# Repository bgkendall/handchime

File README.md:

# HandSTaMp

## Bill of Materials

| Reference | Silkscreen | Part                        | Footprint | Purpose                                        |
|-----------|------------|-----------------------------|-----------|------------------------------------------------|
| C1, C2    | 1µF        | 2 × 1µF ceramic capacitors  | 0603      | Decoupling capacitors for U3                   |
| C3        | 4µ7F       | 4.7µF ceramic capacitor     | 0603      | Bulk decoupling capacitor for U1               |
| C4        | 100nF      | 100nF ceramic capacitor     | 0603      | Decoupling capacitor for U1                    |
| C5        | 100nF      | 100nF ceramic capacitor     | 0603      | Unwanted reset prevention                      |
| D1        | D1         | PMEG2010EA Schottky diode   | SOD-323   | Reverse current protection                     |
| D2, D3    | D2, D3     | 2 × 1N4148 diodes           | SOD-123   | Matrix diodes for SW1/SW2                      |
| F1        | F1         | 500mA fuse                  | 0603      | Current overload protection                    |
| J1        | J1         | HRO TYPE-C-31-M-12 USB port |           | For the pluggings in of USB cables             |
| R1, R2    | 1, 2       | 2 × 5.1kΩ resistors         | 0603      | USB power negotiation (Rd) resistors           |
| R3        | 5k1Ω – P   | 5.1kΩ resistor              | 0603      | OPTIONAL 5V pull-up for RGB data line¹         |
| R4        | 1万Ω       | 10kΩ resistor               | 0603      | Prevention of unwanted boot state              |
| S1, S2    | *None*     | 2 × MX-compatible switches  | MX plate² | Keys for row 0, columns 0/1; mountings for PCB |
| U1        | U1         | STM32C071GBU6               | UFQFPN-28 | ~~Braaaains!~~ Microcontroller                 |
| U2        | U2         | PRTR5V0U2X                  | SOT-143   | ESD protection                                 |
| U3        | U3         | XC6206P332MR-G LDO          | SOT-23-3  | 5V to 3.3V step-down for U1                    |

##### Notes

 1. Remove/do not place R3 (“P”) if not using pin PB0 to drive RGB LEDs (e.g., as a regular matrix pin).
    Pin PB0 must be set to [open drain mode][open-drain].
 2. Three-pin “plate-mount” switches can be used as-is. To use five-pin “PCB-mount” switches,
    the two extra plastic alignment “pins” must be removed.

[open-drain]: https://docs.qmk.fm/drivers/ws2812#open-drain-circuit

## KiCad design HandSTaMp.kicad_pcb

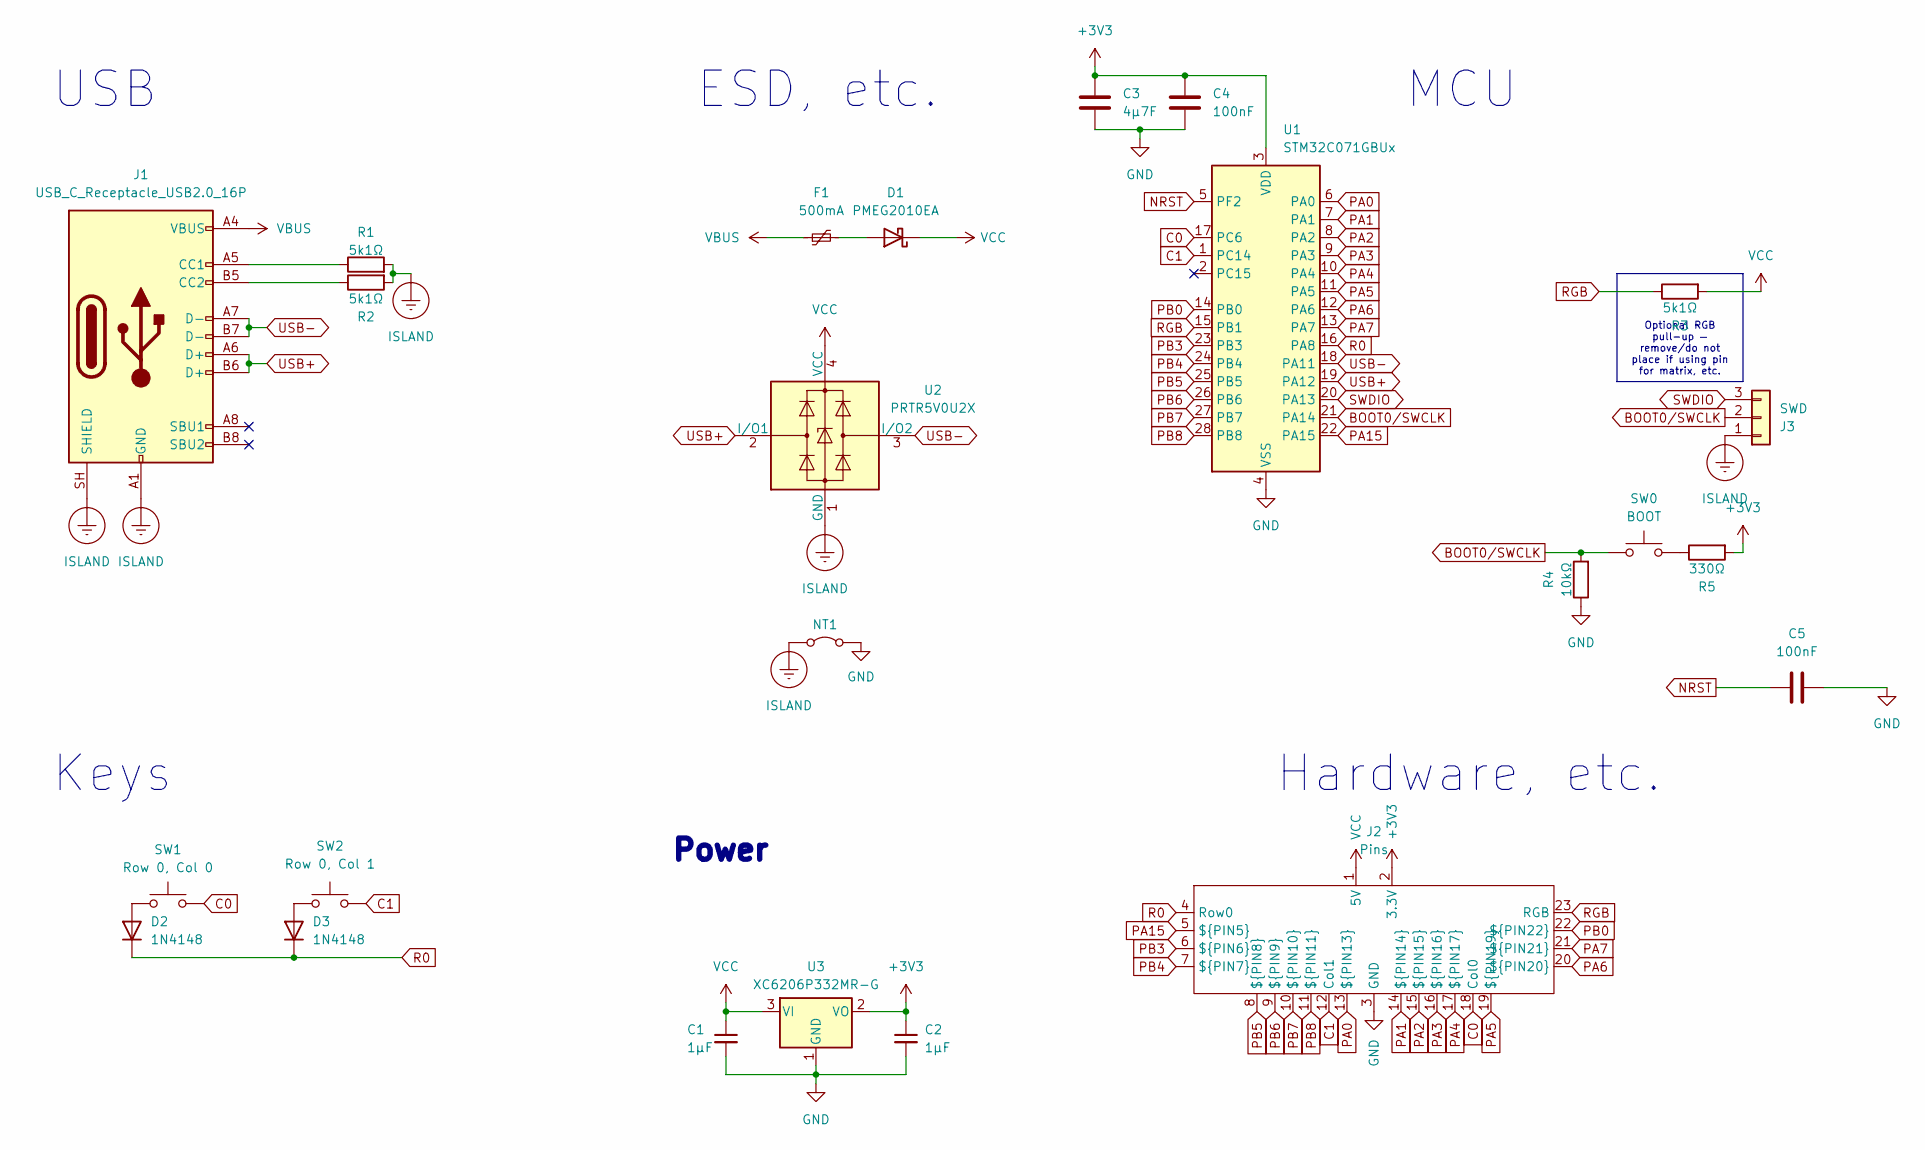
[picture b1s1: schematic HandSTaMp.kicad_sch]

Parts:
C1, C2: 1µF; C_0603_1608Metric; LCSC C52923
C3: 4µ7F; C_0603_1608Metric
C4, C5: 100nF; C_0603_1608Metric
D1: PMEG2010EA; D_SOD-323; LCSC C2837790
D2, D3: 1N4148; D_SOD-123
F1: 500mA; Fuse_0603_1608Metric; LCSC C210357
J1: USB_C_Receptacle_USB2.0_16P; USB_C_Receptacle_HRO_TYPE-C-31-M-12
J2: Pins; HandSTaMp
J3: SWD; SWD+GroundingPoint
NT1: Mounting Hole/Isolated Ground Jumper; NetTie-2_SMD_Pad0.5mm
R1, R2, R3: 5k1Ω; R_0603_1608Metric; LCSC C23186
R4: 10kΩ; R_0603_1608Metric; LCSC C23186
R5: 330Ω; R_0603_1608Metric; LCSC C23186
SW0: BOOT; SW_SPST_B3U-1000P; LCSC C231329
SW1: Row 0, Col 0; SW_MX_1u_PlateMount
SW2: Row 0, Col 1; SW_MX_1u_PlateMount
U1: STM32C071GBUx; QFN-28_4x4mm_P0.5mm
U2: PRTR5V0U2X; SOT-143; LCSC C12333
U3: XC6206P332MR-G; SOT-23-3

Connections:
+3V3: C2.1, C3.1, C4.1, J2.2 (3.3V), R5.2, U1.3 (VDD), U3.2 (VO)
BOOT0/SWCLK: J3.2, R4.2, SW0.1, U1.21 (PA14)
C0: J2.18 (Col0), SW1.1, U1.17 (PC6)
C1: J2.12 (Col1), SW2.1, U1.1 (PC14)
GND: C1.2, C2.2, C3.2, C4.2, C5.2, J2.3 (GND), NT1.2 (B), R4.1, U1.4 (VSS), U3.1 (GND)
ISLAND: J1.A1 (GND), J1.A12 (GND), J1.B1 (GND), J1.B12 (GND), J1.SH (SHIELD), J3.1, NT1.1 (A), R1.2, R2.2, U2.1 (GND)
NRST: C5.1, U1.5 (PF2)
unnamed: D1.2 (A), F1.2
unnamed: D2.2 (A), SW1.2
unnamed: D3.2 (A), SW2.2
unnamed: J1.A5 (CC1), R1.1
unnamed: J1.B5 (CC2), R2.1
unnamed: R5.1, SW0.2
PA0: J2.13 (${PIN13}), U1.6 (PA0)
PA1: J2.14 (${PIN14}), U1.7 (PA1)
PA2: J2.15 (${PIN15}), U1.8 (PA2)
PA3: J2.16 (${PIN16}), U1.9 (PA3)
PA4: J2.17 (${PIN17}), U1.10 (PA4)
PA5: J2.19 (${PIN19}), U1.11 (PA5)
PA6: J2.20 (${PIN20}), U1.12 (PA6)
PA7: J2.21 (${PIN21}), U1.13 (PA7)
PA15: J2.5 (${PIN5}), U1.22 (PA15)
PB0: J2.22 (${PIN22}), U1.14 (PB0)
PB3: J2.6 (${PIN6}), U1.23 (PB3)
PB4: J2.7 (${PIN7}), U1.24 (PB4)
PB5: J2.8 (${PIN8}), U1.25 (PB5)
PB6: J2.9 (${PIN9}), U1.26 (PB6)
PB7: J2.10 (${PIN10}), U1.27 (PB7)
PB8: J2.11 (${PIN11}), U1.28 (PB8)
R0: D2.1 (K), D3.1 (K), J2.4 (Row0), U1.16 (PA8)
RGB: J2.23 (RGB), R3.1, U1.15 (PB1)
SWDIO: J3.3, U1.20 (PA13)
USB+: J1.A6 (D+), J1.B6 (D+), U1.19 (PA12), U2.2 (I/O1)
USB-: J1.A7 (D-), J1.B7 (D-), U1.18 (PA11), U2.3 (I/O2)
VBUS: F1.1, J1.A4 (VBUS), J1.A9 (VBUS), J1.B4 (VBUS), J1.B9 (VBUS)
VCC: C1.1, D1.1 (K), J2.1 (5V), R3.2, U2.4 (VCC), U3.3 (VI)

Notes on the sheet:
Keys
MCU
Hardware, etc.
ESD, etc.
Power
USB
Optional RGB pull-up — remove/do not place if using pin for matrix, etc.

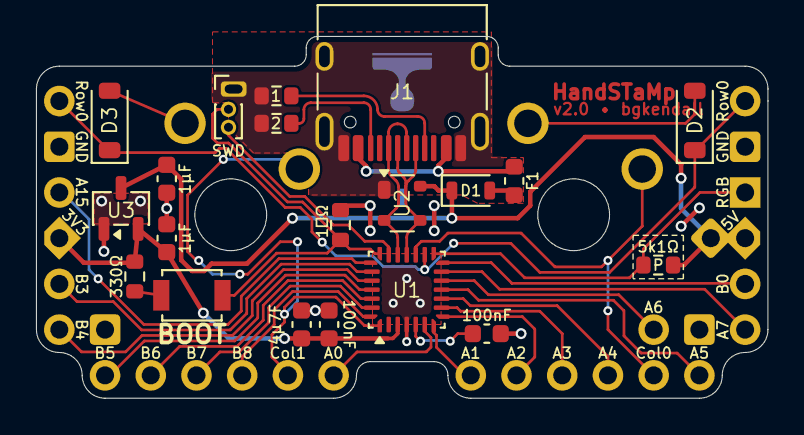
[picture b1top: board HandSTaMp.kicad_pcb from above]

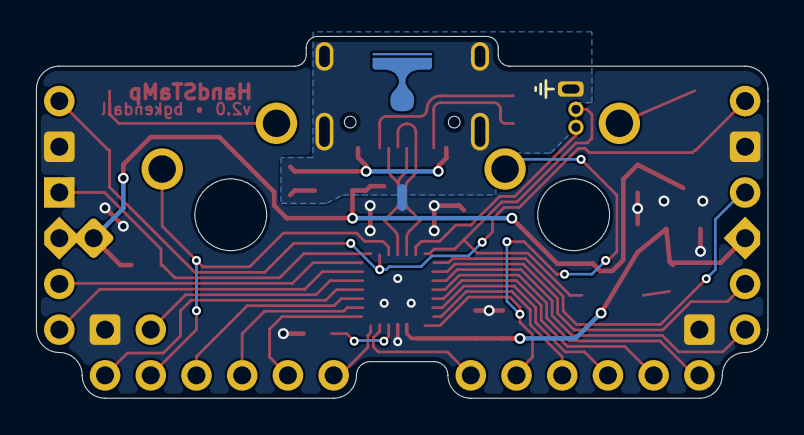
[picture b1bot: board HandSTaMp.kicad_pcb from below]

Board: 2 copper layers, 40.6 x 20.1 mm, 24 parts (3 on the bottom side), 36 nets.

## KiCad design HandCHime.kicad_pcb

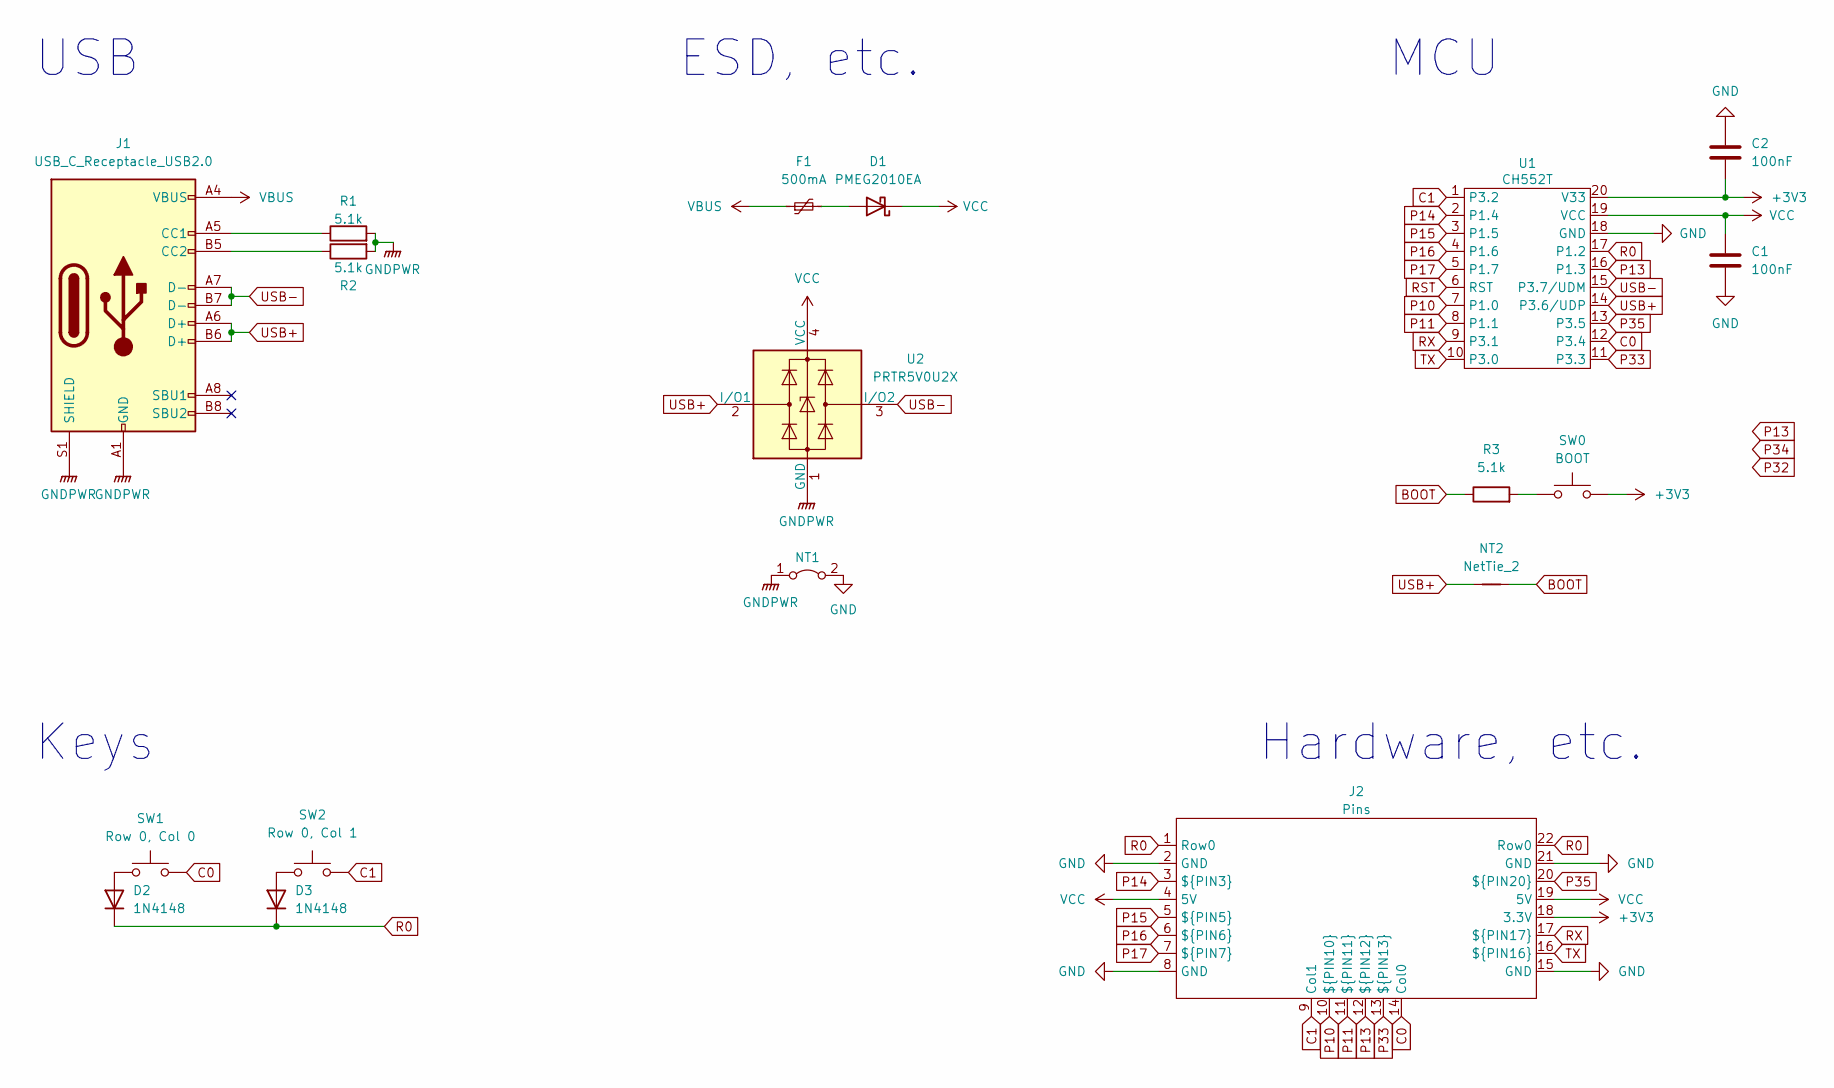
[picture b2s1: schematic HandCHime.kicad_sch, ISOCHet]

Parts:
C1, C2: 100nF; C_0603_1608Metric; LCSC C66501
D1: PMEG2010EA; D_SOD-323; LCSC C2837790
D2, D3: 1N4148; D_SOD-123
F1: 500mA; Fuse_0603_1608Metric; LCSC C210357
J1: USB_C_Receptacle_USB2.0; USB_C_Receptacle_GCT_USB4105-xx-A_16P_TopMnt_Horizontal; LCSC C2840393
J2: Pins; HandCHime
NT1: Mounting Hole/Isolated Ground Jumper; NetTie-2_SMD_Pad0.5mm
NT2: NetTie_2; NetTie-2_SMD_Pad0.254mm
R1, R2, R3: 5.1k; R_0603_1608Metric; LCSC C23186
SW0: BOOT; SW_SPST_B3U-1000P; LCSC C231329
SW1: Row 0, Col 0; SW_MX_1u_PlateMount
SW2: Row 0, Col 1; SW_MX_1u_PlateMount
U1: CH552T; TSSOP-20_4.4x6.5mm_P0.65mm; LCSC C111367
U2: PRTR5V0U2X; SOT-143; LCSC C12333

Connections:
+3V3: C2.1, J2.18 (3.3V), SW0.2, U1.20 (V33)
BOOT: NT2.1, R3.1
C0: J2.14 (Col0), SW1.1, U1.12 (P3.4)
C1: J2.9 (Col1), SW2.1, U1.1 (P3.2)
GND: C1.2, C2.2, J2.2 (GND), J2.8 (GND), J2.15 (GND), J2.21 (GND), NT1.2 (B), U1.18 (GND)
GNDPWR: J1.A1 (GND), J1.A12 (GND), J1.B1 (GND), J1.B12 (GND), J1.S1 (SHIELD), NT1.1 (A), R1.2, R2.2, U2.1 (GND)
unnamed: D1.2 (A), F1.2
unnamed: D2.2 (A), SW1.2
unnamed: D3.2 (A), SW2.2
unnamed: J1.A5 (CC1), R1.1
unnamed: J1.B5 (CC2), R2.1
unnamed: R3.2, SW0.1
P10: J2.10 (${PIN10}), U1.7 (P1.0)
P11: J2.11 (${PIN11}), U1.8 (P1.1)
P13: J2.12 (${PIN12}), U1.16 (P1.3)
P14: J2.3 (${PIN3}), U1.2 (P1.4)
P15: J2.5 (${PIN5}), U1.3 (P1.5)
P16: J2.6 (${PIN6}), U1.4 (P1.6)
P17: J2.7 (${PIN7}), U1.5 (P1.7)
P33: J2.13 (${PIN13}), U1.11 (P3.3)
P35: J2.20 (${PIN20}), U1.13 (P3.5)
R0: D2.1 (K), D3.1 (K), J2.1 (Row0), J2.22 (Row0), U1.17 (P1.2)
RST: U1.6 (RST)
RX: J2.17 (${PIN17}), U1.9 (P3.1)
TX: J2.16 (${PIN16}), U1.10 (P3.0)
USB+: J1.A6 (D+), J1.B6 (D+), NT2.2, U1.14 (P3.6/UDP), U2.2 (I/O1)
USB-: J1.A7 (D-), J1.B7 (D-), U1.15 (P3.7/UDM), U2.3 (I/O2)
VBUS: F1.1, J1.A4 (VBUS), J1.A9 (VBUS), J1.B4 (VBUS), J1.B9 (VBUS)
VCC: C1.1, D1.1 (K), J2.4 (5V), J2.19 (5V), U1.19 (VCC), U2.4 (VCC)

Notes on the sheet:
Keys
MCU
Hardware, etc.
ESD, etc.
USB

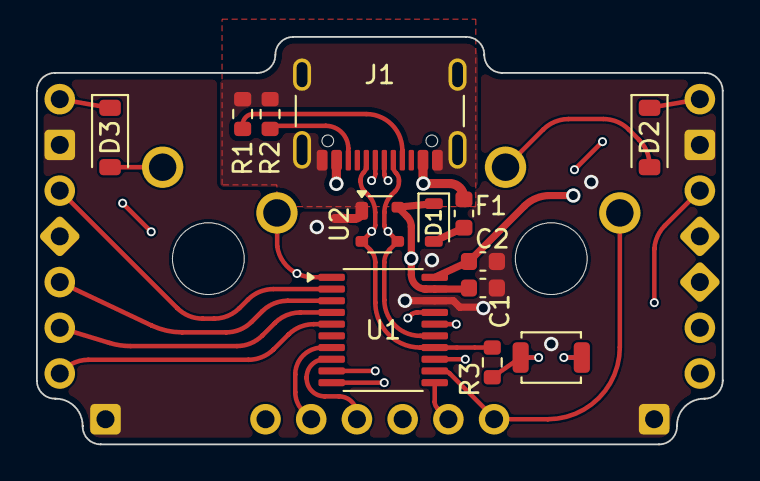
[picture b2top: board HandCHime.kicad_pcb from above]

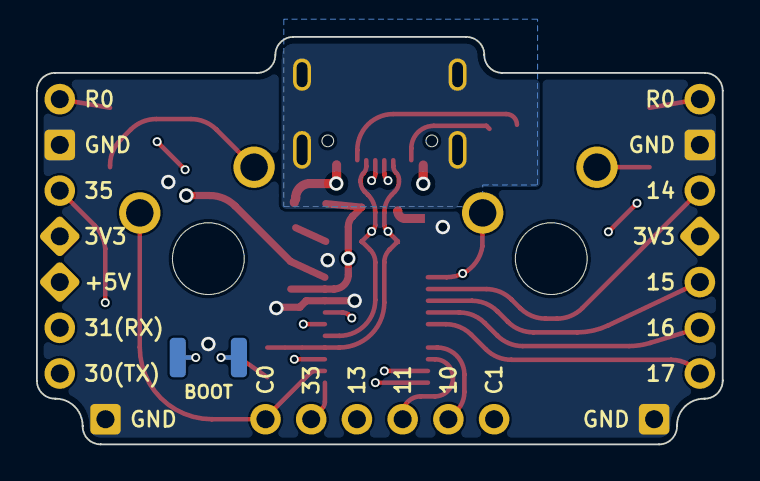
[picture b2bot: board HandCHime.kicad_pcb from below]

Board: 4 copper layers, 38.1 x 22.6 mm, 18 parts (2 on the bottom side), 28 nets.

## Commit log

2024-07-07 Add license
2024-07-07 Add draft of HandCHime PCB
2024-07-07 Try moving MCU to central part of board
2024-07-09 Move MCU to centre of board and reroute
2024-07-09 Add logo
2024-07-10 Straighten VCC track from MCU to pin
    Other routing tweaks
2024-07-14 Use trace for 3V3, other routing tweaks
2024-07-23 Add notches to bottom left and right corners
    This should avoid any supports that might be nearby between switches.
2024-07-23 Correct CH552 schematic symbols
2024-07-23 Update net tie in schematic
2024-07-23 Move switches to centre of board
2024-07-23 Add labels to pins
    Labels are currently on the back silkscreen, which is not the best. However, trying to squeeze them on the front seems optimistic.
2024-07-23 Move fuse away from newly lowered switch
2025-01-25 Reduce default via size
2025-01-25 Remove erroneous button
2025-01-25 Update boot switch
    * Now uses the smaller B3U-1000P switch
    * Alternate pads provided on the keyswitch side so that Boot can be accessed by removing a keycap and poking through LED slot (on compatible switches)
    * Can now reroute C0 to avoid snaking around too much
    * Took advantage of now smaller vias on other traces
2025-01-25 Swap +5 and 3.3V outputs
2025-01-25 Fix part numbers for recently updated components
2025-01-25 Use smaller ESD chip
    USBLC6-2SC6 → PRTR5V0U2X
2025-02-13 Swap Row from P1.3 to P1.2 for better routing
2025-02-13 Minor tweaks
    * Round pads on boot button
    * Add back silkscreen for boot button
    * Improve pad size for Schottky diode (D1)
    * Tune VCC routing
    * Fix DRC errors on net ties
    * Fix board constraints to remove DRC errors on vias
2025-02-13 Move vias away from pin labels
2025-02-13 Redo USB D± routing
2025-12-12 Update KiCad version
2026-03-29 Update to KiCad v10
2026-03-29 Rename from HandCHime to Handchime
    With FAK development being discontinued, it no longer makes sense to use the **CH**552T. With an STM32, HandSTamp would make sense, but there are already a number of projects with “stamp”-based names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
2026-03-29 Update schematic with STM32 version draft
2026-03-30 Update breakout pin symbol and footprint
2026-03-30 Update PCB with STH32 version draft
2026-03-30 Various tweaks and improvements
2026-03-30 Move USB port into required location
2026-03-30 Move board to align with MX grid
2026-03-30 Move components to work with relocated USB port
2026-03-30 Various tweaks
2026-03-31 Add 2-hole SWD access point
2026-03-31 Clean-up edge cuts, tidy routing around NRST
2026-03-31 Add RGB pull-up to edge pin 22
    PB0 has the following timers available for driving RGB LEDs using PWM:
    * TIM3_CH3
    * TIM1_CH2N
2026-03-31 Minor tweaks around U3
2026-03-31 Switch to two-layer stack-up
2026-03-31 Clean-up silkscreens, tweak routing
2026-04-02 Tweak component placement
    Tidy F1 and D1, and swap C3 and C3
2026-04-02 Fix edge pin alignment and improve silkscreen
2026-04-02 Use values instead of references for resistor and capacitor silkscreens
2026-04-02 Remove unused footprints from project library
2026-04-02 Add pad for shield ground connection to (metal) case
2026-04-02 Make grounding connection part of SWD access point
2026-04-02 Tweak routing
2026-04-02 Try to improve routing of Col1 trace
2026-04-04 Tweak edge of ground island fill
2026-04-07 Tweak routing and labelling of CC resistors
2026-04-07 Update labelling on optional RGB pull-op resistor
2026-04-07 Tweak NRST and adjacent routing
2026-04-07 Add draft BOM
2026-04-07 Add missing notation
2026-04-07 Fix resistor values in BOM
2026-04-08 Update outline of ground island; remove QR code
    The QR code was probably too small to be accurately silkscreened. The handchime logo has been moved to that location, and is now no longer blocked by the switches.
2026-04-08 Add one extra GPIO pin access
2026-04-08 Tweaked routing
2026-04-11 Increase middle inset by 5mil
2026-04-11 Change name to HandSTamp
2026-04-11 Update filenames and libraries
